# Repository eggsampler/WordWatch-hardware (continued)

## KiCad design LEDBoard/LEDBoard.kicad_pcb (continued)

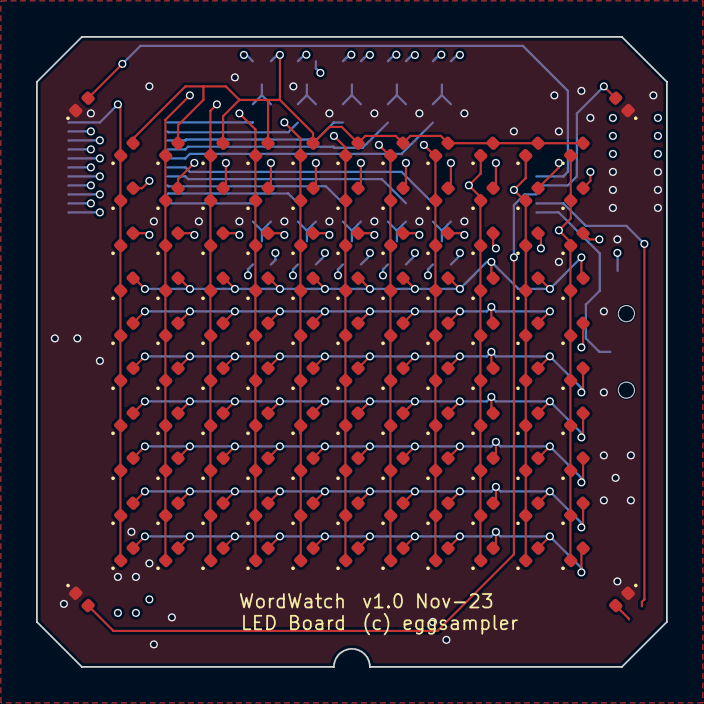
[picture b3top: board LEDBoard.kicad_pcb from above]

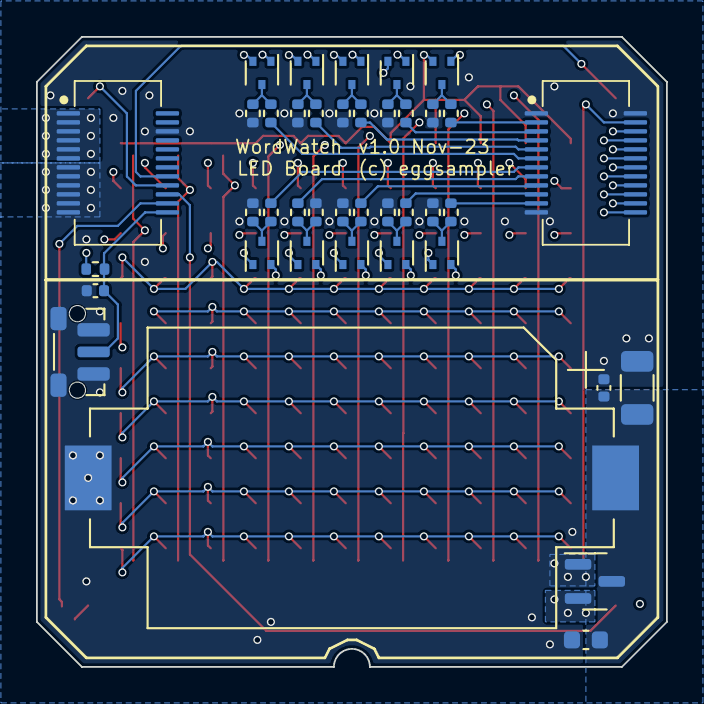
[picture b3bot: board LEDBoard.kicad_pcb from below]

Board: 4 copper layers, 35.0 x 35.0 mm, 154 parts (40 on the bottom side), 49 nets.

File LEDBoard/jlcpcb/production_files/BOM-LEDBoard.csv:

Comment,Designator,Footprint,LCSC
SKRTLA,SW1,SW_Push_1P1T-MP_NO_Horizontal_Alps_SKRTLAE010,C110293
1k,"R13,R14,R15,R16,R17,R18,R19,R20,R21,R22,R23,R24,R25,R26,R27,R28,R29,R30,R31,R32",R_0402_1005Metric,C11702
100uF,C1,C_1206_3216Metric,C15008
AO3401A,Q1,SOT-23,C15127
10uF,C3,C_0603_1608Metric,C19702
DMG1012T,"Q10,Q11,Q2,Q3,Q4,Q5,Q6,Q7,Q8,Q9",SOT-523,C20512
CR2032,BT1,BatteryHolder_Keystone_1060_1x2032,C238069
10k,R7,R_0402_1005Metric,C25744
X0511FVS-24AS-LPV01,"J1,J2",X0511FVS-24AS-LPV01,C2925346
LED_Small,"D1,D10,D100,D101,D102,D103,D104,D105,D106,D107,D108,D109,D11,D110,D111,D112,D113,D114,D12,D13,D14,D15,D16,D17,D18,D19,D2,D20,D21,D22,D23,D24,D25,D26,D27,D28,D29,D3,D30,D31,D32,D33,D34,D35,D36,D37,D38,D39,D4,D40,D41,D42,D43,D44,D45,D46,D47,D48,D49,D5,D50,D51,D52,D53,D54,D55,D56,D57,D58,D59,D6,D60,D61,D62,D63,D64,D65,D66,D67,D68,D69,D7,D70,D71,D72,D73,D74,D75,D76,D77,D78,D79,D8,D80,D81,D82,D83,D84,D85,D86,D87,D88,D89,D9,D90,D91,D92,D93,D94,D95,D96,D97,D98,D99",LED_0402_1005Metric,C434448
1uF,"C2,C4",C_0402_1005Metric,C52923

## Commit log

2023-10-31 Commit design files
2023-11-05 Minor board updates
2023-11-08 Remove LED driver
2023-11-08 Small fixes for plotting
2023-11-08 Remove all via in pad on controller board where possible
2023-11-09 Remove all via in pad on led board where possible
2023-11-11 Change led matrix routing for sinking current through mcu, sourcing from battery
2023-11-11 Fix programming board plot, add extra library files
2023-11-11 Update control board silkscreen
2023-11-17 Add PNG outputs
